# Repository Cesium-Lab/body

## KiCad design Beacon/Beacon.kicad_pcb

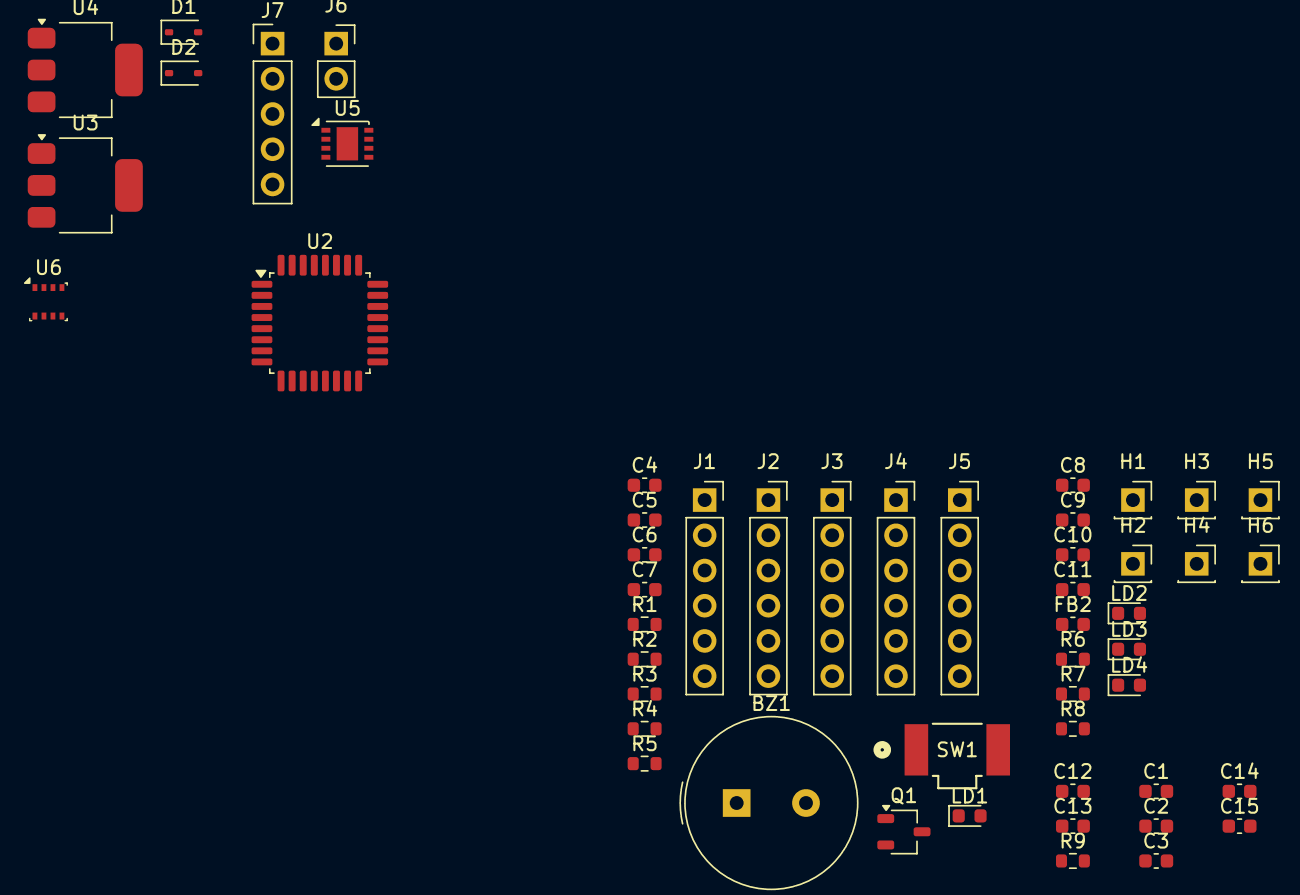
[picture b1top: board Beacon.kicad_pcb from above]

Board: 2 copper layers, 52 parts (0 on the bottom side), 39 nets, no tracks yet.

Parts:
BZ1: PS1240P02BT; Buzzer_TDK_PS1240P02BT_D12.2mm_H6.5mm
C1, C12, C13: 0.1uF; C_0603_1608Metric
C2: 10nF; C_0603_1608Metric
C3: 2.2uF; C_0603_1608Metric
C4, C5, C6, C7, C8, C9, C14, C15: 100nF; C_0603_1608Metric
C10, C11: 10uF; C_0603_1608Metric
D1, D2: BAT60JFILM; D_SOD-323
FB2: FerriteBead_Small; C_0603_1608Metric
H1, H2, H3, H4, H5, H6: PAD; PinSocket_1x01_P2.54mm_Vertical
J1, J2: Conn_01x06_Pin; PinSocket_1x06_P2.54mm_Vertical
J3, J4, J5: Conn_01x02_Socket; PinSocket_1x06_P2.54mm_Vertical
J6: Conn_01x02_Socket; PinSocket_1x02_P2.54mm_Vertical
J7: Conn_01x05_Socket; PinHeader_1x05_P2.54mm_Vertical
LD1, LD2: Green; LED_0603_1608Metric
LD3: Red; LED_0603_1608Metric
LD4: Blue; LED_0603_1608Metric
Q1: NMOS (2N7002NXAKR); TSOT-23
R1: 100; R_0603_1608Metric
R2: 510; R_0603_1608Metric
R3, R4: 2.2k; R_0603_1608Metric
R5: 10K; R_0603_1608Metric
R6: 1; R_0603_1608Metric
R7: 30; R_0603_1608Metric
R8: 20; R_0603_1608Metric
R9: 120; R_0603_1608Metric
SW1: KSS221G; SW_KSS221GLFS_CNK
U2: STM32F042K6Tx; LQFP-32_7x7mm_P0.8mm
U3: LD1117S50TR_SOT223; SOT-223-3_TabPin2
U4: LD1117S33TR_SOT223; SOT-223-3_TabPin2
U5: MCP2542FDxMF; DFN-8-1EP_3x3mm_P0.65mm_EP1.55x2.4mm
U6: BME280; Bosch_LGA-8_2.5x2.5mm_P0.65mm_ClockwisePinNumbering

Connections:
+3.3V: C1.1, C2.1, C3.1, C5.1, C6.1, C11.1, C14.2, C15.2, FB2.1, H4.1, LD2.2 (A), R1.1, R3.1, R4.1, U2.1 (VDD), U2.17 (VDDIO2), U4.2 (VO), U6.2 (CSB), U6.5 (SDO), U6.6 (VDDIO), U6.8 (VDD)
+3V3: C12.2, U5.5 (VIO)
+5V: C9.1, C10.1, C13.1, U3.3 (VI), U4.3 (VI), U5.3 (VDD)
/BME280/SCL: J1.5, R3.2, U2.3 (PF1), U6.4 (SCK)
/BME280/SDA: J1.4, R4.2, U2.2 (PF0), U6.3 (SDI)
/CAN/CANH: J7.3, R9.1, U5.7 (CANH)
/CAN/CANL: J7.4, R9.2, U5.6 (CANL)
/CAN/CAN_RX: J6.1, U2.21 (PA11), U5.4 (RXD)
/CAN/CAN_TX: J6.2, U2.22 (PA12), U5.1 (TXD)
/ICM-42670-P/MISO: J1.2, U2.12 (PA6)
/ICM-42670-P/MOSI: J1.1, U2.13 (PA7)
/ICM-42670-P/SCK: J1.3, U2.11 (PA5)
/STM32 F042/BOOT0: R5.1, U2.31 (PB8)
/STM32 F042/BUZZ: BZ1.1 (+), Q1.3 (S)
/STM32 F042/BUZZ_EN: Q1.2 (G), U2.14 (PB0)
/STM32 F042/LED1: LD1.2 (A), U2.15 (PB1)
/STM32 F042/NRST: C4.1, SW1.2, U2.4 (NRST)
/STM32 F042/PA15: J2.1, U2.25 (PA15)
/STM32 F042/PB3: J2.6, U2.26 (PB3)
/STM32 F042/PB4: J2.5, U2.27 (PB4)
/STM32 F042/PB5: J2.4, U2.28 (PB5)
/STM32 F042/PB6: J2.3, U2.29 (PB6)
/STM32 F042/PB7: J2.2, U2.30 (PB7)
/STM32 F042/RX1: J3.2, U2.19 (PA9)
/STM32 F042/RX2: J4.2, U2.9 (PA3)
/STM32 F042/SWCLK: J5.2, U2.24 (PA14)
/STM32 F042/SWDIO: J5.1, U2.23 (PA13)
/STM32 F042/TX1: J3.1, U2.20 (PA10)
/STM32 F042/TX2: J4.1, U2.8 (PA2)
GND: BZ1.2 (-), C1.2, C2.2, C3.2, C4.2, C5.2, C6.2, C7.2, C8.2, C9.2, C10.2, C11.2, C12.1, C13.2, C14.1, C15.1, H1.1, H2.1, H3.1, J1.6, J7.5, R2.2, R5.2, R6.2, R7.2, R8.2, SW1.1, U2.16 (VSS), U2.32 (VSSA), U3.1 (GND), U4.1 (GND), U5.2 (VSS), U5.8 (STBY), U5.9 (VSS), U6.1 (GND), U6.7 (GND)
unnamed: C8.1, D1.1 (K), D2.1 (K), U3.2 (VO)
unnamed: LD1.1 (K), R2.1
unnamed: LD2.1 (K), R6.1
unnamed: LD3.1 (K), R7.1
unnamed: LD4.1 (K), R8.1
unnamed: Q1.1 (D), R1.2
VBAT: D2.2 (A), H5.1, LD3.2 (A)
VBUS: D1.2 (A), H6.1, J7.2, LD4.2 (A)
VDDA: C7.1, FB2.2, U2.5 (VDDA)

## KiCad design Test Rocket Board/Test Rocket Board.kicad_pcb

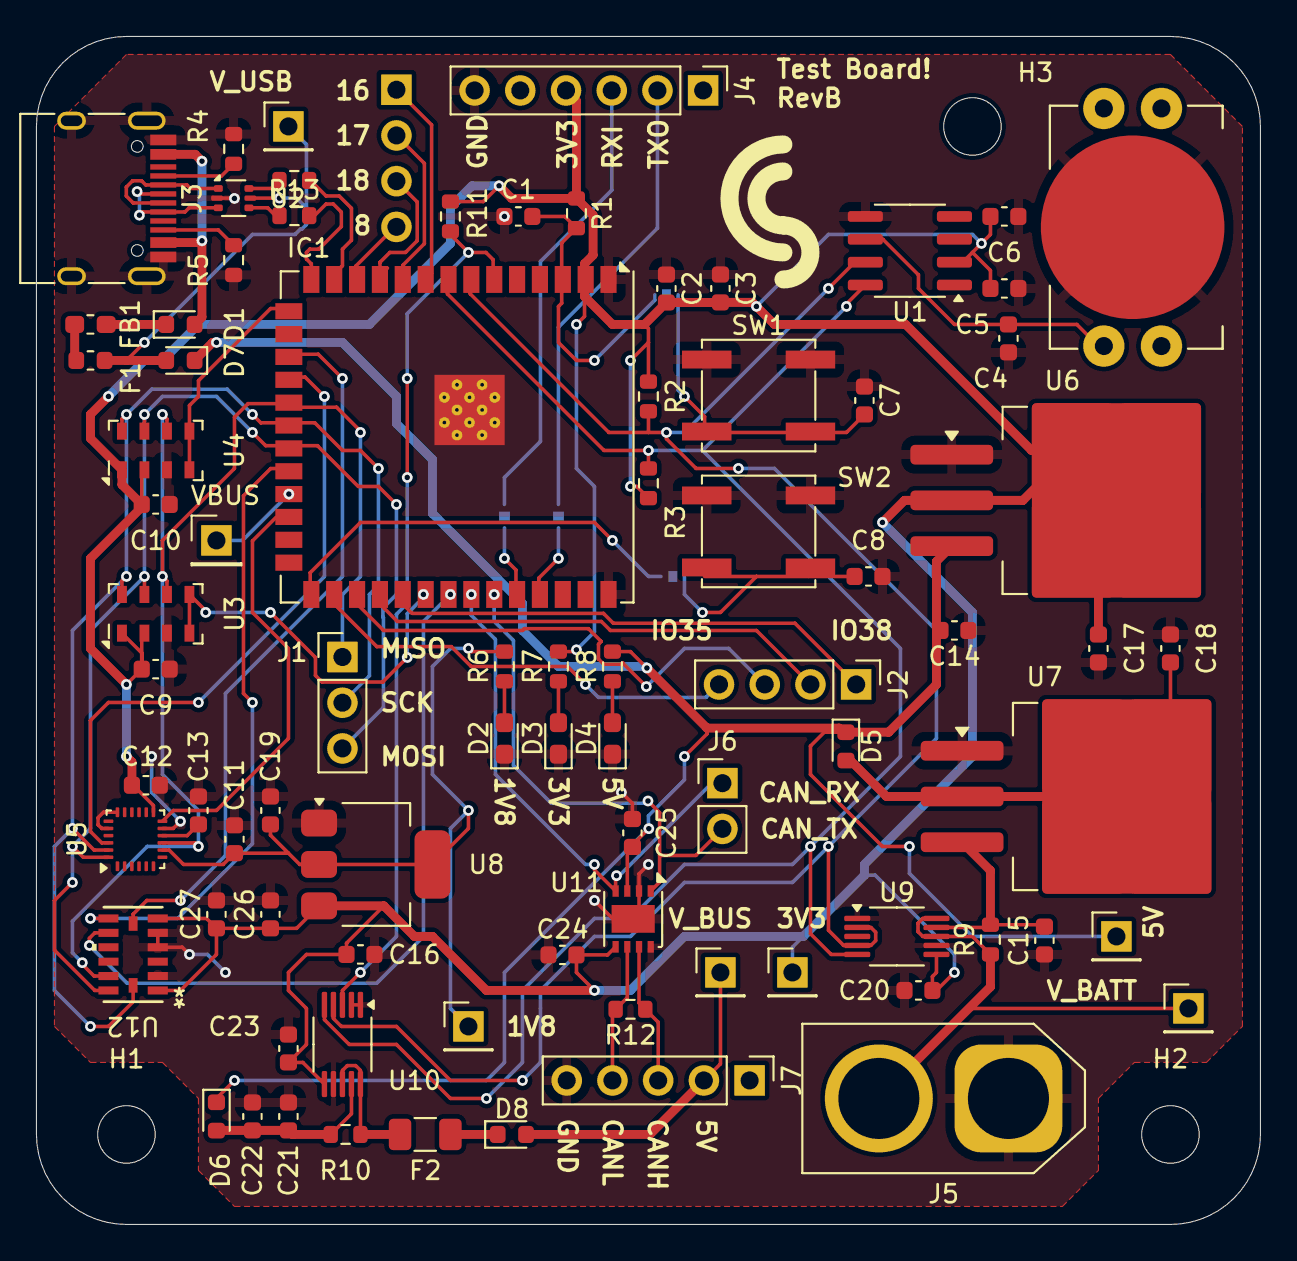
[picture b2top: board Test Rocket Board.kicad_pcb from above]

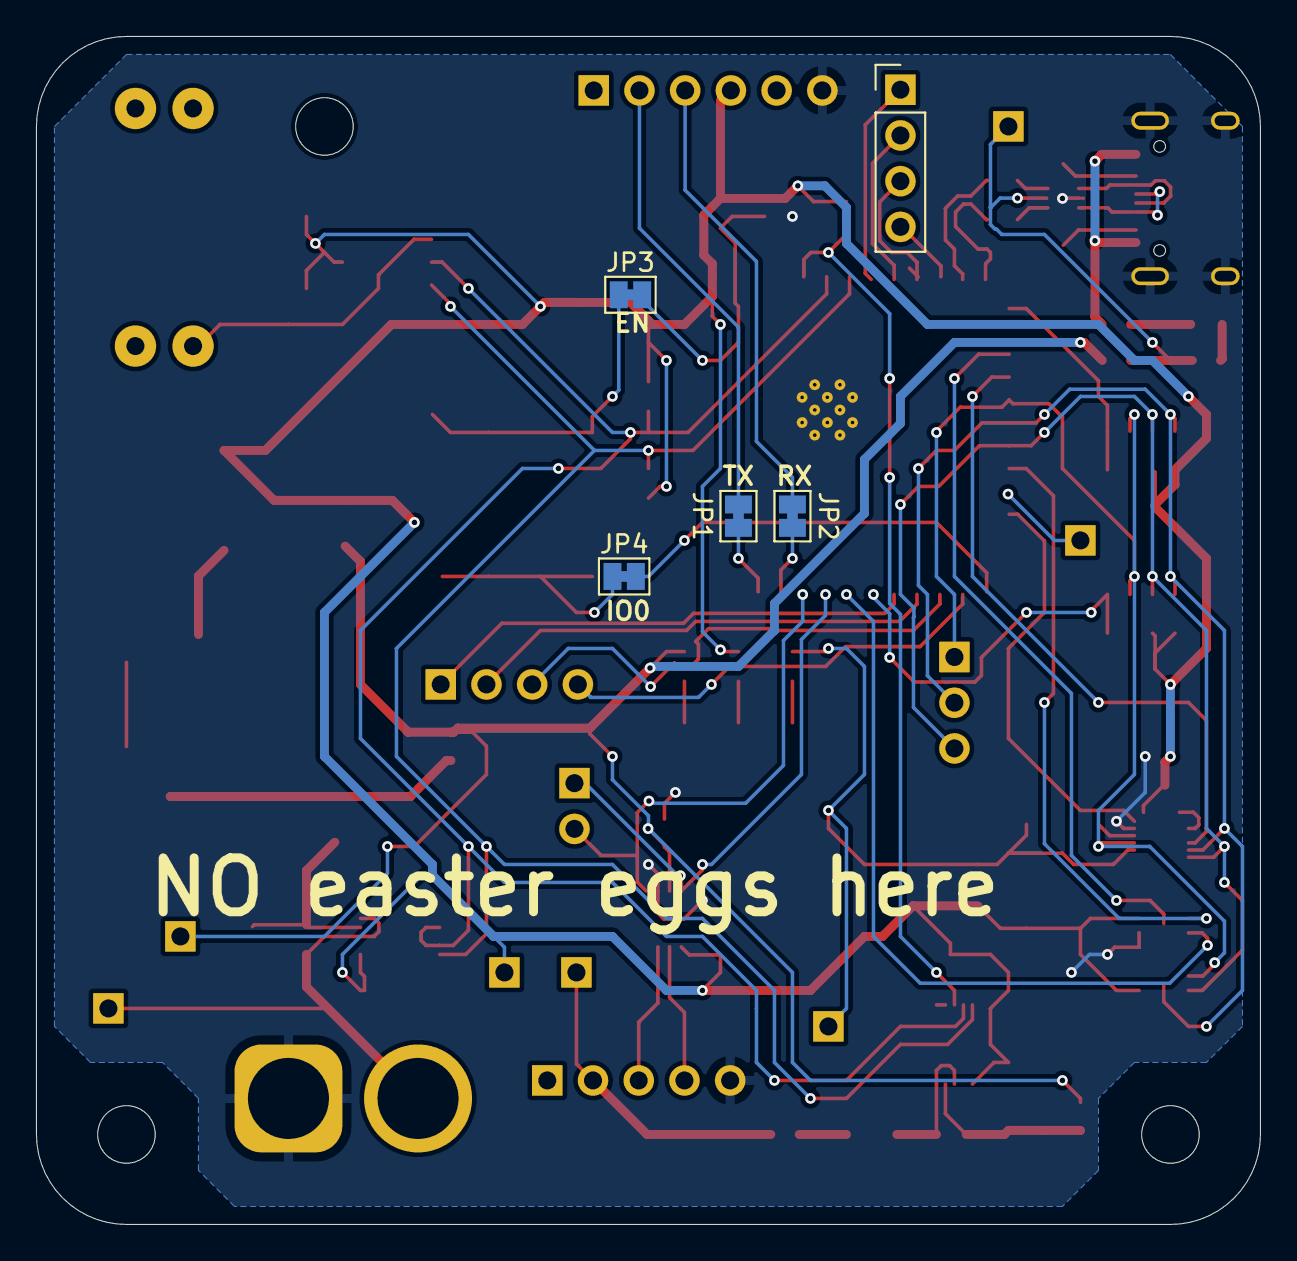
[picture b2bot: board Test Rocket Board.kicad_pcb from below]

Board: 2 copper layers, 68.0 x 66.0 mm, 90 parts (5 on the bottom side), 62 nets.

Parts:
5V1: 5V; PinHeader_1x01_P2.54mm_Vertical
BT1: BAT-HLD-012-THM; BAT_BAT-HLD-012-THM
C1, C5, C26: 1uF; C_0603_1608Metric
C2, C19: 22uF; C_0603_1608Metric
C3, C4, C6, C7, C8, C9, C10, C11, C12, C13, C20, C22, C23, C24, C25, C27: 0.1uF; C_0603_1608Metric
C14, C15, C16, C17, C18: 10uF; C_0603_1608Metric
C21: 47uF; C_0603_1608Metric
D1, D5, D6, D7, D8: D; D_0603_1608Metric
D2, D3, D4: GREEN; LED_0603_1608Metric_Pad1.05x0.95mm_HandSolder
F1: 5V/3A; Fuse_0603_1608Metric
F2: Polyfuse; Fuse_1206_3216Metric
FB1: BLM21PG221; L_0603_1608Metric_Pad1.05x0.95mm_HandSolder
H1, H2, H3: MountingHole; MountingHole_3.2mm_M3
IC1: ESP32-S3-WROOM-1U-N16; ESP32-S3-WROOM-1U
J1: Conn_01x03_Pin; PinHeader_1x03_P2.54mm_Vertical
J2, J8: Conn_01x04_Pin; PinHeader_1x04_P2.54mm_Vertical
J3: USB_C_Receptacle_USB2.0_16P; USB_C_Receptacle_HRO_TYPE-C-31-M-12
J4: Conn_01x06_Socket; PinHeader_1x06_P2.54mm_Vertical
J5: Conn_01x02; AMASS_XT60-M_1x02_P7.20mm_Vertical
J6: Conn_01x02_Socket; PinHeader_1x02_P2.54mm_Vertical
J7: Conn_01x05_Socket; PinHeader_1x05_P2.54mm_Vertical
JP1, JP2, JP3, JP4: SolderJumper_2_Bridged; SolderJumper-2_P1.3mm_Bridged_Pad1.0x1.5mm
R1: 10k; R_0603_1608Metric
R2, R3: 4.7k; R_0603_1608Metric
R4, R5: 5.1k; R_0603_1608Metric
R6: 220; R_0603_1608Metric
R7, R8, R11: 1k; R_0603_1608Metric
R9, R10: 200m; R_0603_1608Metric
R12: 120; R_0603_1608Metric
R13, R14: 22; R_0603_1608Metric
SW1, SW2: SW_Push; SW_SPST_EVPBF
TP1: V_BUS; PinHeader_1x01_P2.54mm_Vertical
TP2: 3V3; PinHeader_1x01_P2.54mm_Vertical
TP3: V_BATT; PinHeader_1x01_P2.54mm_Vertical
TP4: 1V8; PinHeader_1x01_P2.54mm_Vertical
TP5: V_USB; PinHeader_1x01_P2.54mm_Vertical
U1: DS3232M; SOIC-8_3.9x4.9mm_P1.27mm
U2: USBLC6-2P6; SOT-666
U3, U4: MS5607-02BA; LGA-8_3x5mm_P1.25mm
U5: ICM-20948; InvenSense_QFN-24_3x3mm_P0.4mm
U6: LM1085-3.3; TO-263-3_TabPin2
U7: LM1085-5.0; TO-263-3_TabPin2
U8: AMS1117-1.8; SOT-223-3_TabPin2
U9, U10: INA233; VSSOP-10_3x3mm_P0.5mm
U11: MCP2542FDxMF; DFN-8-1EP_3x3mm_P0.65mm_EP1.55x2.4mm
U12: ADXL375BCCZ-RL7; LGA_CC-14-1_ADI
VBUS: VBUS; PinHeader_1x01_P2.54mm_Vertical

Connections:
5V_BUS: D8.2 (A), J7.2, TP1.1
+1V8: C11.2, C19.1, R6.2, TP4.1, U5.8 (VDDIO), U8.2 (VO)
+3V3: C2.2, C3.2, C5.1, C6.1, C9.1, C10.1, C12.1, C16.1, C17.2, C20.1, C23.1, C24.2, C26.1, C27.1, IC1.2 (3V3), J4.4, R1.1, R2.1, R3.1, R7.2, R11.2, TP2.1, U1.2 (VCC), U3.1 (VDD), U3.2 (PS), U4.1 (VDD), U4.2 (PS), U5.13 (VDD), U6.2 (VO), U8.3 (VI), U9.6 (VS), U10.6 (VS), U11.5 (VIO), U12.1 (VDDI/O), U12.6 (VS)
+5V: 5V1.1, C14.2, C25.1, D5.1 (K), D6.1 (K), D7.1 (K), R8.2, U6.3 (VI), U11.3 (VDD)
/ADXL375/CS: IC1.17 (IO9), U12.7 (*CS)
/ADXL375/INT1: IC1.22 (IO14), U12.8 (INT1)
/ADXL375/INT2: IC1.33 (IO40), U12.9 (INT2)
/ADXL375/MISO: IC1.19 (IO11), J1.1, U3.6 (SDO), U4.6 (SDO), U5.9 (SDO/AD0), U12.12 (SDO/ALTADDRESS)
/ADXL375/MOSI: IC1.21 (IO13), J1.3, U3.7 (SDI/SDA), U4.7 (SDI/SDA), U5.24 (SDA/SDI), U12.13 (SDA/SDI/SDIO)
/ADXL375/SCK: IC1.20 (IO12), J1.2, U3.8 (SCLK), U4.8 (SCLK), U5.23 (SCL/SCLK), U12.14 (SCL/SCLK)
/Barometer 1/CS: IC1.32 (IO39), U3.4 (CSB), U3.5 (CSB)
/Barometer 2/CS: IC1.15 (IO3), U4.4 (CSB), U4.5 (CSB)
/CAN Bus/CAN_RX: IC1.34 (IO41), J6.1, U11.4 (RXD)
/CAN Bus/CAN_TX: IC1.35 (IO42), J6.2, U11.1 (TXD)
/Flashing/CC1: J3.A5 (CC1), R4.1
/Flashing/CC2: J3.B5 (CC2), R5.1
/Flashing/D+: IC1.14 (IO20), R13.2
/Flashing/D-: IC1.13 (IO19), R14.2
/Flashing/EN: C1.2, IC1.3 (EN), JP3.2 (B), R1.2
/Flashing/ESP_RX: IC1.36 (RXD0), JP2.2 (B)
/Flashing/ESP_TX: IC1.37 (TXD0), JP1.1 (A)
/Flashing/IO0: IC1.27 (IO0), JP4.2 (B)
/Flashing/SVD+: R13.1, U2.4 (I/O2)
/Flashing/SVD-: R14.1, U2.6 (I/O1)
/Flashing/USB+: J3.A6 (D+), J3.B6 (D+), U2.3 (I/O2)
/Flashing/USB-: J3.A7 (D-), J3.B7 (D-), U2.1 (I/O1)
/Flashing/VBUS: D1.2 (A), J3.A4 (VBUS), J3.A9 (VBUS), J3.B4 (VBUS), J3.B9 (VBUS)
/Flashing/V_USB: D7.2 (A), F1.1, TP5.1, U2.5 (VBUS)
/IMU (2g-16g)/CS: IC1.18 (IO10), U5.22 (~CS)
/IMU (2g-16g)/INT: IC1.24 (IO47), U5.12 (INT1)
/MCU/INA_INT: IC1.6 (IO6), R11.1, U10.3 (~Alert)
/MCU/IO8: IC1.12 (IO8), J8.4
/MCU/IO16: IC1.9 (IO16), J8.1
/MCU/IO17: IC1.10 (IO17), J8.2
/MCU/IO18: IC1.11 (IO18), J8.3
/MCU/IO35: IC1.28 (IO35), J2.4
/MCU/IO36: IC1.29 (IO36), J2.3
/MCU/IO37: IC1.30 (IO37), J2.2
/MCU/IO38: IC1.31 (IO38), J2.1
/MCU/SCL: IC1.8 (IO15), R3.2, U1.8 (SCL), U9.5 (SCL), U10.5 (SCL)
/MCU/SDA: IC1.7 (IO7), R2.2, U1.7 (SDA), U9.2 (A0), U9.4 (SDA), U10.4 (SDA)
/MCU/VBUS_TEST: IC1.23 (IO21), VBUS.1
/Power/5V_LDO: C18.2, D5.2 (A), U7.2 (VO)
/Power/BATT_INPUT: J5.2, R9.1, TP3.1, U9.8 (Vbus), U9.10 (Vin+)
/Power/V_BATT: C15.2, R9.2, U7.3 (VI), U9.9 (Vin-)
/Power/V_BUS_Out: C21.1, C22.1, D6.2 (A), R10.2, U10.9 (Vin-)
CANH: J7.3, R12.1, U11.7 (CANH)
CANL: J7.4, R12.2, U11.6 (CANL)
GND: BT1.N, C1.1, C2.1, C3.1, C4.1, C5.2, C6.2, C7.1, C8.1, C9.2, C10.2, C11.1, C12.2, C13.2, C14.1, C15.1, C16.2, C17.1, C18.1, C19.2, C20.2, C21.2, C22.2, C23.2, C24.1, C25.2, C26.2, C27.2, D2.1 (K), D3.1 (K), D4.1 (K), IC1.1 (GND_1), IC1.40 (GND_2), IC1.41 (GND_3), J3.A1 (GND), J3.A12 (GND), J3.B1 (GND), J3.B12 (GND), J3.S1 (SHIELD), J4.6, J5.1, J7.5, R4.2, R5.2, SW1.1, SW2.1, U1.5 (GND), U2.2 (GND), U3.3 (GND), U4.3 (GND), U5.11 (FSYNC), U5.18 (GND), U5.20 (GND), U6.1 (GND), U7.1 (GND), U8.1 (GND), U9.1 (A1), U9.7 (GND), U10.1 (A1), U10.2 (A0), U10.7 (GND), U11.2 (VSS), U11.8 (STBY), U11.9 (VSS), U12.2 (GND), U12.4 (GND), U12.5 (GND)
unnamed: D1.1 (K), FB1.1
unnamed: D2.2 (A), R6.1
unnamed: D3.2 (A), R7.1
unnamed: D4.2 (A), R8.1
unnamed: D8.1 (K), F2.1
unnamed: F1.2, FB1.2
unnamed: J4.2, JP1.2 (B)
unnamed: J4.3, JP2.1 (A)
unnamed: C7.2, JP3.1 (A), SW1.2
unnamed: C8.2, JP4.1 (A), SW2.2
unnamed: BT1.P1, C4.2, U1.6 (VBAT)
unnamed: C13.1, U5.10 (REGOUT)
unnamed: F2.2, R10.1, U10.8 (Vbus), U10.10 (Vin+)

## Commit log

2026-04-20 hardware
2026-04-20 idk what this is
2026-04-20 idk what this is (#1)
